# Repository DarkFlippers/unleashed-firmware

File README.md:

# Flipper Zero Firmware community repo

Welcome to [Flipper Zero](https://flipperzero.one/)'s Firmware repo! Our goal is to create nice and clean code along with good documentation, to make it a pleasure for everyone to work with. This repo will become completely public closer to the device shipping date. 

# Update firmware

Flipper Zero's firmware consists of two components: Bootloader and main firmware. Bootloader controls firmware update process over USB. You need working bootloader installed before update firmware over USB.

1. Download latest [Firmware](https://update.flipperzero.one/full_firmware_latest.bin)

2. Reboot Flipper to Bootloader 
 - Press and hold `← Left` + `↩ Back` for reset 
 - Release `← Left` and keep holding `↩ Back` until blue LED lights up
 - Release `↩ Back`

1. Run `dfu-util -D firmware.bin -a 0 -s 0x08008000:leave`

## Build from source

You can run firmware locally (with HAL stub):

* `docker-compose exec dev make -C firmware TARGET=local APP_TEST=1 run` for running tests
* `docker-compose exec dev make -C firmware TARGET=local APP_*=1 run` for running examples (see `applications/applications.mk` for list of applications/examples)

Or you can use your dev. board:

`docker-compose exec dev make -C firmware TARGET=f2 APP_*=1 flash` for build and flash dev board (see `applications/applications.mk` for list of applications/examples)

# Links
* Task tracker: [Jira](https://flipperzero.atlassian.net/)
* Discord server: [flipperzero.one/discord](https://flipperzero.one/discord)
* Project website: [flipperzero.one](https://flipperzero.one)
* Kickstarter page: [kickstarter.com](https://www.kickstarter.com/projects/flipper-devices/flipper-zero-tamagochi-for-hackers)
* Forum: [forum.flipperzero.one](https://forum.flipperzero.one/)

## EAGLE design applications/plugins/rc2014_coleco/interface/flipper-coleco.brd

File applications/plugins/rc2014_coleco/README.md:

# RC2014 ColecoVision Controller for Flipper Zero

A Flipper Zero application and [RC2014] module allowing the Flipper to be used as a controller for ColecoVision games on
the [RC2014].

## Running ColecoVision Games on the RC2014

A full tutorial is out of scope here, but briefly, you will need a [RC2014] with J. B. Langston's [TMS9918A Video Card]
and [SN76489 Sound Card], as well as some way to launch ColecoVision ROMs.

Note that if you're using the standard pageable ROM module (e.g. if you're using the stock Pro kit), you will need to
[modify it](https://github.com/jblang/TMS9918A/issues/12) in order for the TMS9918A module to work on the ColecoVision
port addresses.

## Hardware Setup

The [interface](interface) directory contains Eagle schematics for a RC2014 module that handles the controller port
addressing for two players, breaking out the 8 data line inputs as well as the mode select line. This can actually be
used for different controller implementations and is slightly more flexible than the actual [ColecoVision] spec.

To use this with the Flipper Zero and this application, a GPIO board is needed to provide hardware multiplexing for the
data lines. A schematic for the GPIO board will be added to this repository soon.

## Building the FAP

1. Clone the [flipperzero-firmware] repository.
2. Create a symbolic link in `applications_user` named `coleco`, pointing to this repository.
3. Compile with `./fbt fap_coleco`.
4. Copy `build/f7-firmware-D/.extapps/coleco.fap` to `apps/Misc` on the SD card (directly or using [qFlipper]).

[RC2014]: https://rc2014.co.uk/
[TMS9918A Video Card]: https://github.com/jblang/TMS9918A
[SN76489 Sound Card]: https://github.com/jblang/SN76489
[ColecoVision]: http://www.atarihq.com/danb/files/CV-Tech.txt
[flipperzero-firmware]: https://github.com/flipperdevices/flipperzero-firmware
[qFlipper]: https://flipperzero.one/update

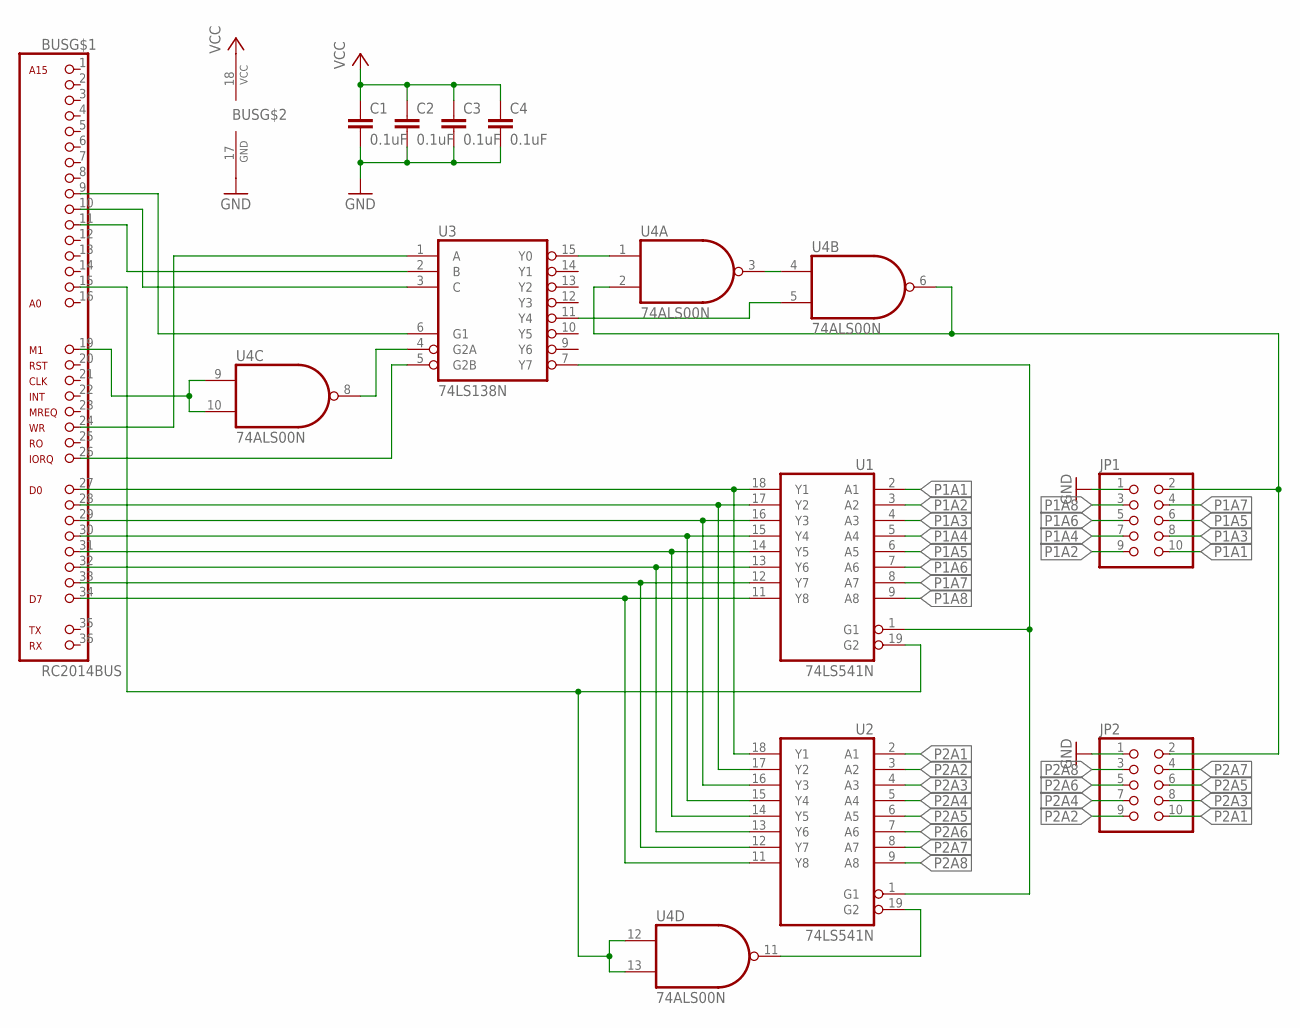
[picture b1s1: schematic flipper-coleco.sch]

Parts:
BUS: RC2014BUS; 1X39
C1, C2, C3, C4: 0.1uF; C050-024X044
JP1, JP2: PINHD-2X5; 2X05
U1, U2: 74LS541N; DIL20
U3: 74LS138N; DIL16
U4: 74ALS00N; DIL14

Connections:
A1: BUS.15 (A1), U1.19 (G2), U4.12 (I0), U4.13 (I1)
GND: BUS.17 (GND), C1.2, C2.2, C3.2, C4.2, JP1.1, JP2.1, U1.10 (GND), U2.10 (GND), U3.8 (GND), U4.7 (GND)
unnamed: BUS.34 (D7), U1.11 (Y8), U2.11 (Y8)
unnamed: BUS.33 (D6), U1.12 (Y7), U2.12 (Y7)
unnamed: BUS.32 (D5), U1.13 (Y6), U2.13 (Y6)
unnamed: BUS.31 (D4), U1.14 (Y5), U2.14 (Y5)
unnamed: BUS.30 (D3), U1.15 (Y4), U2.15 (Y4)
unnamed: BUS.29 (D2), U1.16 (Y3), U2.16 (Y3)
unnamed: BUS.28 (D1), U1.17 (Y2), U2.17 (Y2)
unnamed: BUS.27 (D0), U1.18 (Y1), U2.18 (Y1)
unnamed: BUS.24 (WR), U3.1 (A)
unnamed: BUS.11 (A5), U3.2 (B)
unnamed: BUS.10 (A6), U3.3 (C)
unnamed: BUS.9 (A7), U3.6 (G1)
unnamed: BUS.26 (IORQ), U3.5 (G2B)
unnamed: U3.4 (G2A), U4.8 (O)
unnamed: BUS.19 (M1), U4.9 (I0), U4.10 (I1)
unnamed: U1.1 (G1), U2.1 (G1), U3.7 (Y7)
unnamed: U4.3 (O), U4.4 (I0)
unnamed: U3.15 (Y0), U4.1 (I0)
unnamed: U3.11 (Y4), U4.5 (I1)
unnamed: JP1.2, JP2.2, U4.2 (I1), U4.6 (O)
unnamed: U2.19 (G2), U4.11 (O)
P1A1: JP1.10, U1.2 (A1)
P1A2: JP1.9, U1.3 (A2)
P1A3: JP1.8, U1.4 (A3)
P1A4: JP1.7, U1.5 (A4)
P1A5: JP1.6, U1.6 (A5)
P1A6: JP1.5, U1.7 (A6)
P1A7: JP1.4, U1.8 (A7)
P1A8: JP1.3, U1.9 (A8)
P2A1: JP2.10, U2.2 (A1)
P2A2: JP2.9, U2.3 (A2)
P2A3: JP2.8, U2.4 (A3)
P2A4: JP2.7, U2.5 (A4)
P2A5: JP2.6, U2.6 (A5)
P2A6: JP2.5, U2.7 (A6)
P2A7: JP2.4, U2.8 (A7)
P2A8: JP2.3, U2.9 (A8)
VCC: BUS.18 (VCC), C1.1, C2.1, C3.1, C4.1, U1.20 (VCC), U2.20 (VCC), U3.16 (VCC), U4.14 (VCC)

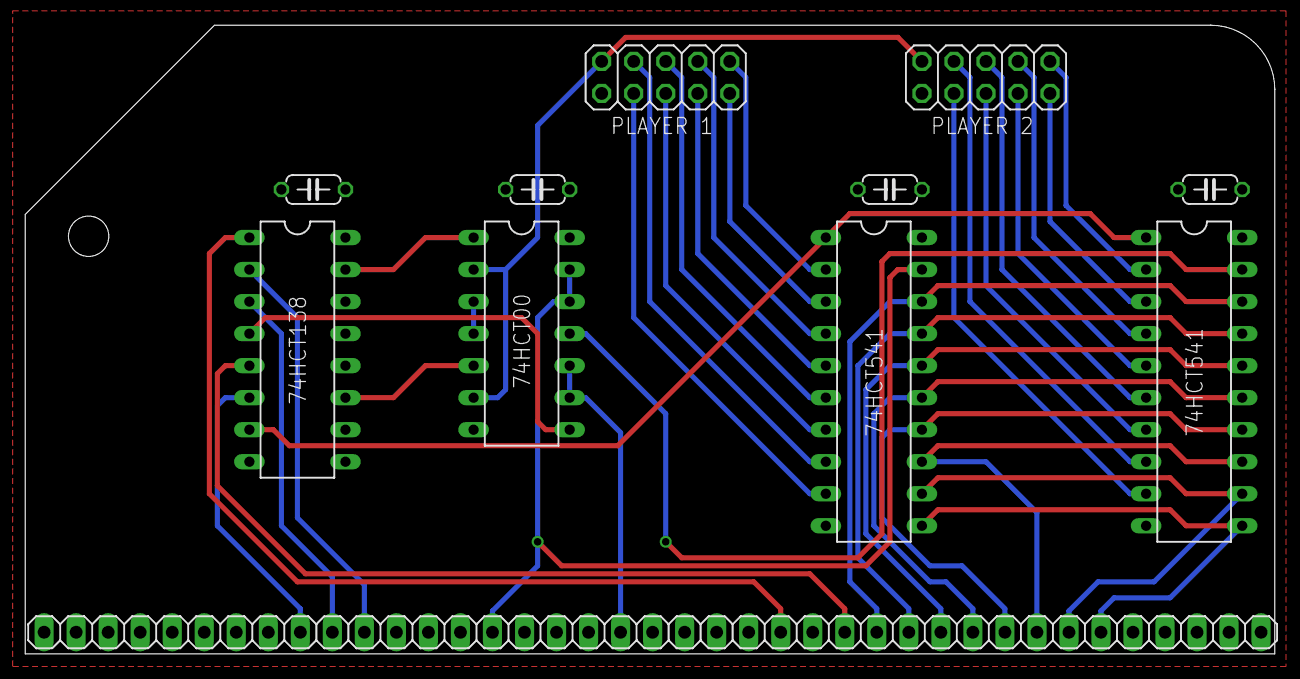
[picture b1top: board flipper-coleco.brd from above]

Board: 2 copper layers, 99.1 x 49.9 mm, 11 parts (0 on the bottom side), 40 nets.
